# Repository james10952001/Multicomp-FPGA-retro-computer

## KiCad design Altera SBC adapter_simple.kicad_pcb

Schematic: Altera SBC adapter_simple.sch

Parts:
C1, C3: 100n; SM0603
C7: 4.7n; SM0603
JP1: 28P; SIL-2
JP2: 24P; SIL-2
P1: RGB_VID; Header_Friction_Lock-6_Vert
P2: Comp_Vid; RCA_RCJ_series
P3: PS/2; Mini_DIN-6_MD-6006
P4: LVTTL Serial 1; SIL-6
P5: LVTTL Serial 2; SIL-5
P6: Audio; SIL-2
P7: I/O; pin_array_14x2
P8: CONN_ALTERA_MIN_BRD_128; Altera_FPGA_mini_brd
R1, R2, R3, R4: 470R; SM0603
R5, R6, R7: 680R; SM0603
R8: 1k; SM0603
R9: 3.3k; SM0603
R13, R14: 10k; SM0603
SD1: SD_MMC_MICRO; Micro_SD_Amphenol_101-00660-68-6
U1: SRAM/ROM; DIP-32__600_ELL

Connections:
+3.3V: C1.1, C3.1, JP1.1, JP2.1, P3.4, P4.2, P5.2, P7.28, P8.PA27, P8.PA28, P8.PB28, P8.PC28, P8.PD27, P8.PD28, R13.2, R14.2, SD1.4, U1.32
/A0: P8.PC10, U1.12
/A1: P8.PC12, U1.11
/A2: P8.PC14, U1.10
/A3: P8.PC16, U1.9
/A4: P8.PC18, U1.8
/A5: P8.PC20, U1.7
/A6: P8.PC22, U1.6
/A7: P8.PC24, U1.5
/A8: P8.PC23, U1.27
/A9: P8.PC21, U1.26
/A10: P8.PC15, U1.23
/A11: P8.PC19, U1.25
/A12: P8.PD22, U1.4
/A13: JP1.2, P8.PD16, U1.28
/A14: P8.PD21, U1.3
/A15: P8.PD6, U1.31
/A16: P8.PD23, U1.2
/A17: JP2.2, P8.PD17, U1.30
/A18: P8.PD15, U1.1
/Audio: P7.26, P8.PD24, R9.1
/CE: P8.PC13, U1.22
/CTS1: P4.6, P8.PB15
/C_Sync: P8.PB4, R8.1
/D0: P8.PC8, U1.13
/D1: P8.PC6, U1.14
/D2: P8.PC4, U1.15
/D3: P8.PC3, U1.17
/D4: P8.PC5, U1.18
/D5: P8.PC7, U1.19
/D6: P8.PC9, U1.20
/D7: P8.PC11, U1.21
/H_Sync: P1.3, P8.PA23
/OE: P8.PC17, U1.24
/PIN26: P7.25, P8.PD18
/PIN40: P7.23, P8.PA1
/PIN41: P7.24, P8.PA2
/PIN42: P7.21, P8.PA3
/PIN43: P7.22, P8.PA4
/PIN44: P7.19, P8.PA5
/PIN45: P7.20, P8.PA6
/PIN47: P7.17, P8.PA7
/PIN48: P7.18, P8.PA8
/PIN51: P7.15, P8.PA9
/PIN52: P7.16, P8.PA10
/PIN53: P7.13, P8.PA11
/PIN55: P7.14, P8.PA12
/PIN57: P7.11, P8.PA13
/PIN58: P7.12, P8.PA14
/PIN59: P7.9, P8.PA15
/PIN60: P7.10, P8.PA16
/PIN73: P7.8, P8.PB3
/PIN76: P7.7, P8.PB6
/PIN79: P7.6, P8.PB7
/PIN80: P7.4, P8.PB8
/PIN81: P7.2, P8.PB9
/PIN88: P7.1, P8.PB12
/PIN89: P7.3, P8.PB13
/PIN90: P7.5, P8.PB14
/PS2CLK: P3.5, P8.PB10, R14.1
/PS2DAT: P3.1, P8.PB11, R13.1
/RTS1: P4.3, P8.PB25
/RTS2: P5.3, P8.PB19
/RXD1: P4.4, P8.PB23
/RXD2: P5.4, P8.PB21
/TXD1: P4.5, P8.PB24
/TXD2: P5.5, P8.PB22
/V_Sync: P1.2, P8.PA24
/VidB0: P8.PA18, R5.1
/VidB1: P8.PA17, R2.1
/VidG0: P8.PA20, R6.1
/VidG1: P8.PA19, R3.1
/VidR0: P8.PA22, R7.1
/VidR1: P8.PA21, R4.1
/Video: P8.PB5, R1.1
/WE: P8.PD4, U1.29
GND: C1.2, C3.2, C7.2, P1.1, P2.1, P3.3, P3.7, P4.1, P5.1, P6.1, P7.27, P8.PA25, P8.PA26, P8.PB1, P8.PB2, P8.PB26, P8.PB27, P8.PC1, P8.PC2, P8.PC26, P8.PC27, P8.PD1, P8.PD2, P8.PD8, P8.PD9, P8.PD10, P8.PD25, P8.PD26, SD1.6, SD1.9, SD1.10, SD1.11, U1.16
unnamed: P8.PB20, SD1.2
unnamed: P8.PB16, SD1.7
unnamed: P1.5, R3.2, R6.2
unnamed: P1.4, R4.2, R7.2
unnamed: C7.1, P6.2 (PM), R9.2
unnamed: P2.2 (PM), R1.2, R8.2
unnamed: P1.6, R2.2, R5.2
unnamed: P8.PB17, SD1.3
unnamed: P8.PB18, SD1.5

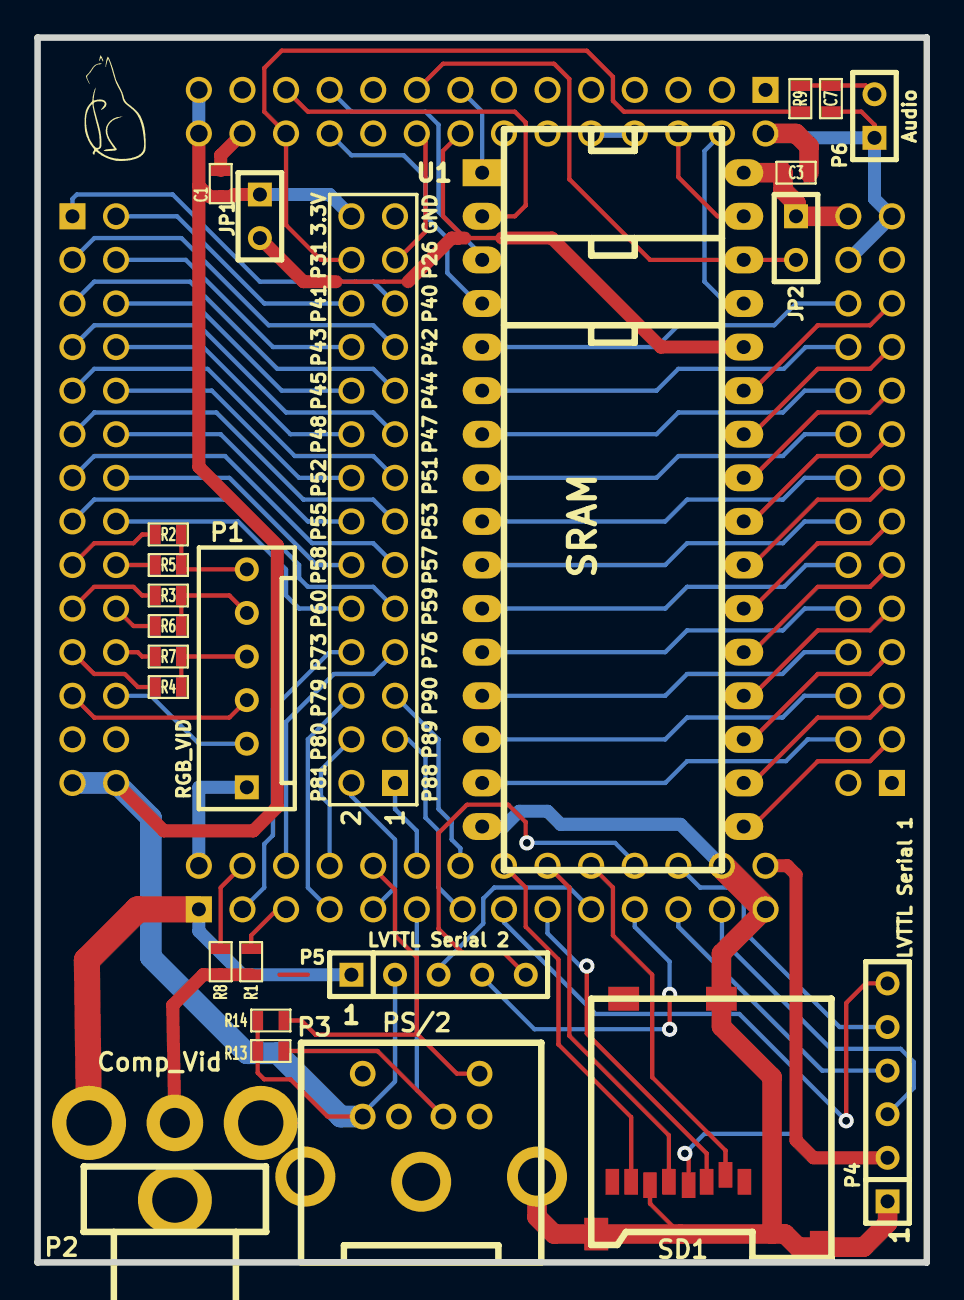
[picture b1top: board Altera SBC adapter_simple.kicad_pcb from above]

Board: 2 copper layers, 51.8 x 71.4 mm, 27 parts (0 on the bottom side), 86 nets.

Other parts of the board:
VAL: REF; cat_300

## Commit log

2018-11-11 Initial public release

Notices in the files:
Altera SBC adapter_simple.kicad_pcb:
FPGA RETRO-COMPUTER INTERFACE (c)2015 James Sweet
